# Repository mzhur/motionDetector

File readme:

Первая версия датчика wi-fi датчика движения из говна и палок

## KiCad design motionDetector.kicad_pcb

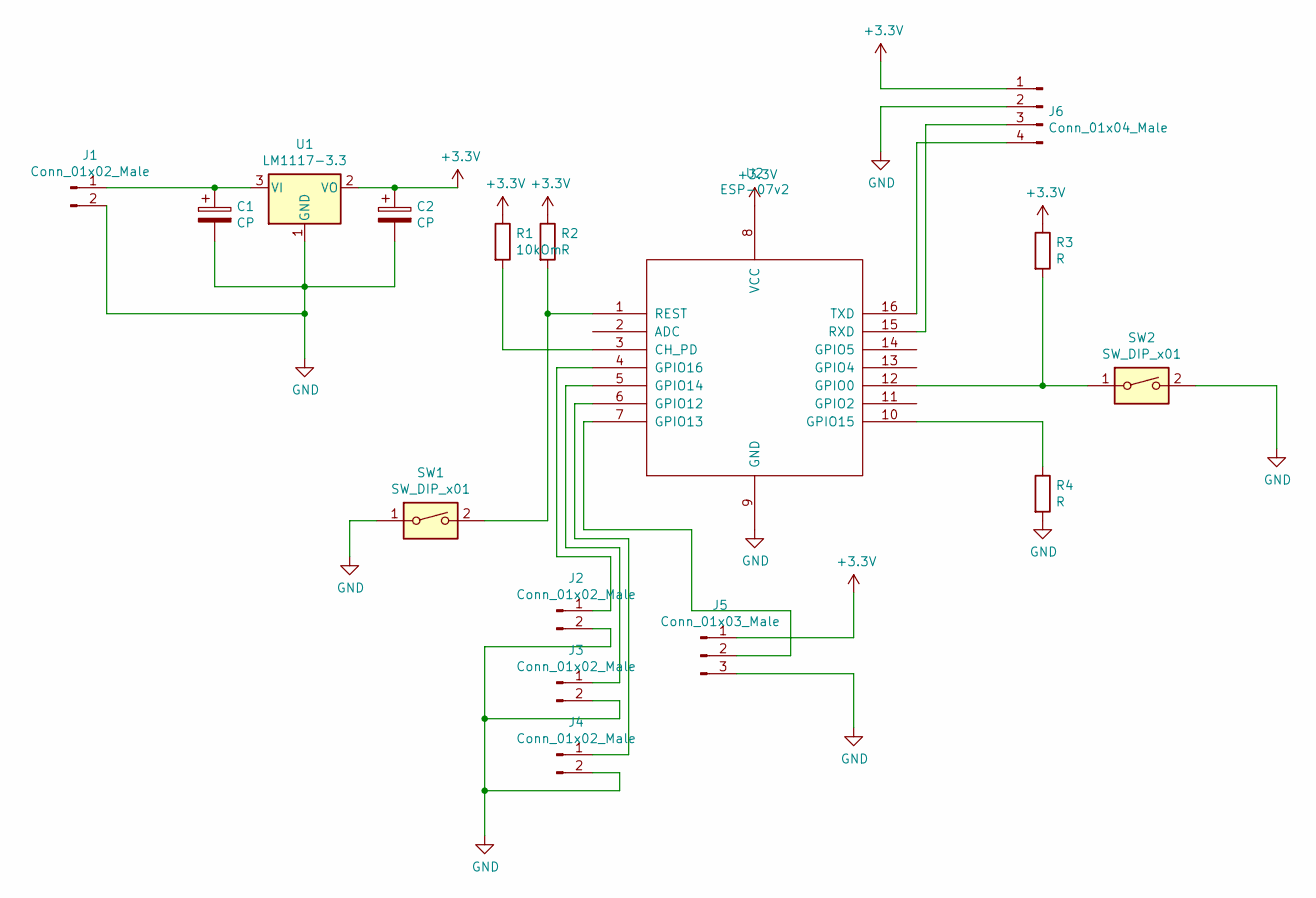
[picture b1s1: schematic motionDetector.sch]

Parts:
C1, C2: CP; CP_EIA-7343-31_Kemet-D_Pad2.25x2.55mm_HandSolder
J1, J2, J3, J4: Conn_01x02_Male; PinHeader_1x02_P2.54mm_Vertical
J5: Conn_01x03_Male; PinHeader_1x03_P2.54mm_Vertical
J6: Conn_01x04_Male; PinHeader_1x04_P2.54mm_Vertical
R1: 10kOm; R_1206_3216Metric
R2, R3, R4: R; R_1206_3216Metric
SW1, SW2: SW_DIP_x01; SW_DIP_SPSTx01_Piano_10.8x4.1mm_W7.62mm_P2.54mm
U1: LM1117-3.3; TO-252-2
U2: ESP-07v2

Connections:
+3V3: C2.1, J5.1, J6.1, R1.1, R2.1, R3.1, U1.2 (VO), U2.8 (VCC)
GND: C1.2, C2.2, J1.2, J2.2, J3.2, J4.2, J5.3, J6.2, R4.2, SW1.1, SW2.2, U1.1 (GND), U2.9 (GND)
unnamed: C1.1, J1.1, U1.3 (VI)
unnamed: J2.1, U2.4 (GPIO16)
unnamed: J3.1, U2.5 (GPIO14)
unnamed: J4.1, U2.6 (GPIO12)
unnamed: J5.2, U2.7 (GPIO13)
unnamed: J6.3, U2.15 (RXD)
unnamed: J6.4, U2.16 (TXD)
unnamed: R1.2, U2.3 (CH_PD)
unnamed: R2.2, SW1.2, U2.1 (REST)
unnamed: R3.2, SW2.1, U2.12 (GPIO0)
unnamed: R4.1, U2.10 (GPIO15)

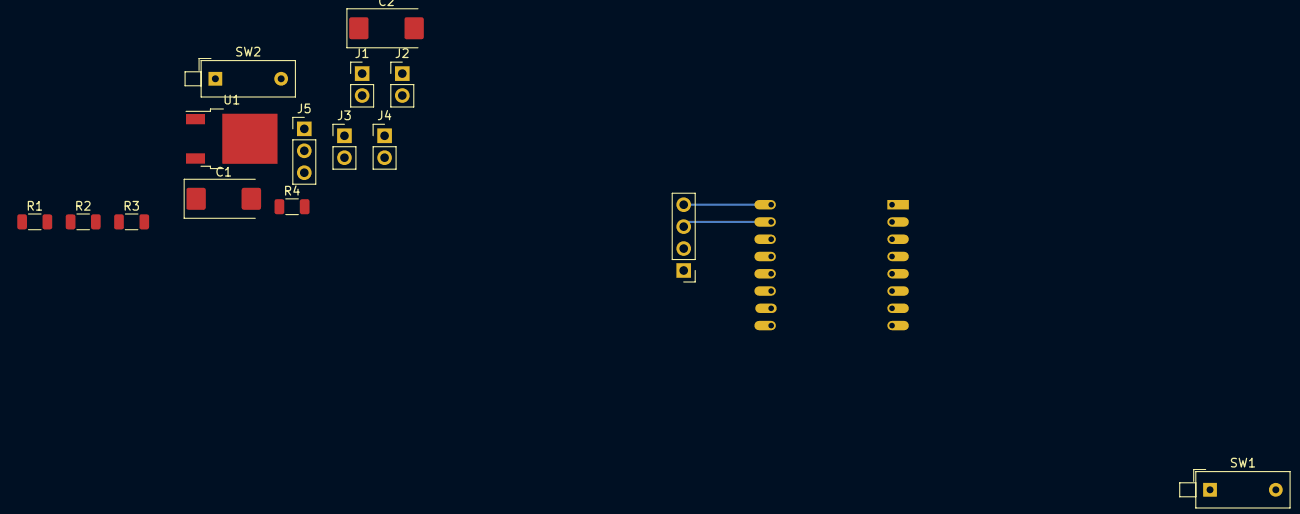
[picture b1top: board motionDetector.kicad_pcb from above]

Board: 2 copper layers, 16 parts (1 on the bottom side), 13 nets.

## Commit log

2020-12-01 v0 shema - done pcb - none
2020-12-02 adding LECENSE
